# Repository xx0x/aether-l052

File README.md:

# Æther L052

A development board using the STM32L052K8Ux, optimized for low-power use. Its form factor matches the Adafruit Feather series.

## Schematic

*Click to see the full-size PDF*

## Specifications

### Microcontroller

| Name             | STM32L052K8Ux       |
| ---------------- | ------------------- |
| Core             | ARM Cortex M0+      |
| Flash Size       | 64 kB               |
| RAM Size         | 8 kB                |
| Clock Frequency  | 32 MHz              |
| Peripherals      | USB, SPI, I2C, UART |
| External Crystal | None                |

STM32L052K8U6 = –40 to 85 °C  
STM32L052K8U7 = –40 to 105 °C  
STM32L052K8U3 = –40 to 125 °C  

### Voltage Regulator

| Name              | MCP1711T-33I/OT |
| ----------------- | --------------- |
| Output Voltage    | 3.3 V           |
| Output Current    | 150 mA          |
| Quiescent Current | 600 nA          |

### Lithium Battery Charger

| Name           | MCP73832T-2ACI/OT     |
| -------------- | --------------------- |
| Charge Current | 100 mA (set using R4) |
| Charge State   | Available through PB8 |

## Why it exists?

There was no entry-level development board for the STM32L052 series, especially for the compact STM32L052K8Ux variant.

## Where to get it?

Æther L052 is open source and not sold in shops. You can build your own; all required files are in the `pcb` folder. If you are a manufacturer, you may reuse the design under the License, or contact me first if you prefer.

## Code examples

Look at the [Æther L052 Examples](https://github.com/xx0x/aether-l052-examples) repository.

## License

CERN-OHL-P-2.0 license

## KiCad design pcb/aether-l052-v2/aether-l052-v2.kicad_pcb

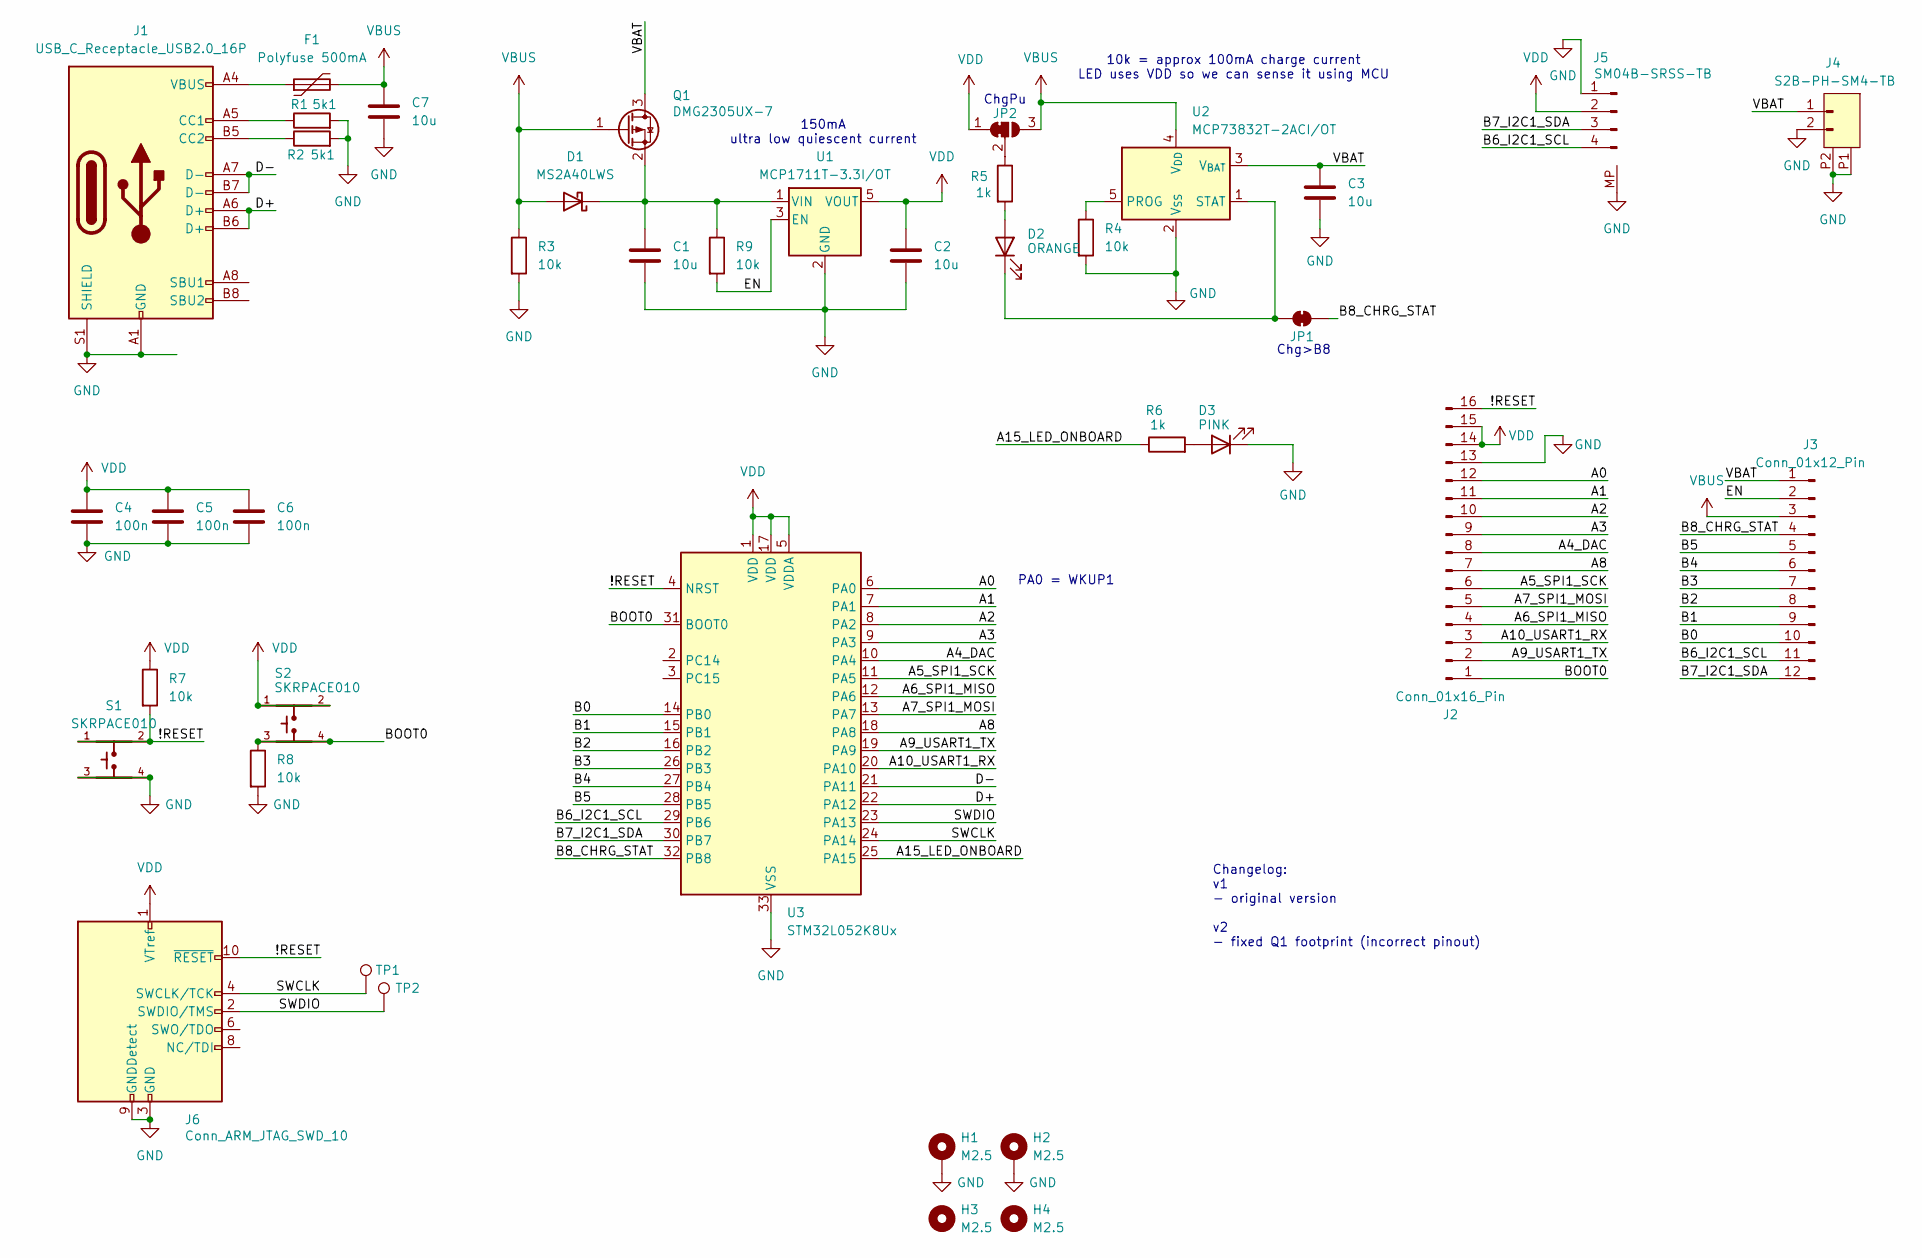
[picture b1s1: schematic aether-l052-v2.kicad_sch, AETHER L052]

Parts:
C1, C2, C3, C7: 10u; C_0805_2012Metric; LCSC C15850
C4, C5, C6: 100n; C_0603_1608Metric; LCSC C14663
D1: MS2A40LWS; D_SOD-323; LCSC C7380001
D2: ORANGE; LED_0603_1608Metric; LCSC C2286
D3: PINK; LED_0603_1608Metric; LCSC C2290
F1: Polyfuse 500mA; Fuse_0805_2012Metric; LCSC C883109
H1, H2: M2.5; MountingHole_2.5mm_Pad_Small
H3, H4: M2.5; MountingHole_2.5mm
J1: USB_C_Receptacle_USB2.0_16P; USB_C_Receptacle_XKB_U262-16XN-4BVC11; LCSC C393939
J2: Conn_01x16_Pin; PinHeader_1x16_P2.54mm_Vertical_NoSilk
J3: Conn_01x12_Pin; PinHeader_1x12_P2.54mm_Vertical_NoSilk
J4: S2B-PH-SM4-TB; S2B-PH-SM4-TB_LF__SN_; LCSC C295747
J5: SM04B-SRSS-TB; JST_SH_SM04B-SRSS-TB_1x04-1MP_P1.00mm_Horizontal; LCSC C160404
J6: Conn_ARM_JTAG_SWD_10; PinHeader_2x05_P1.27mm_Vertical_SMD; LCSC C41376037
JP1: SolderJumper_2_Bridged; SolderJumper-2_P1.3mm_Bridged_RoundedPad1.0x1.5mm
JP2: SolderJumper_3_Bridged12; SolderJumper-3_P1.3mm_Bridged12_RoundedPad1.0x1.5mm
Q1: DMG2305UX-7; SOT-23
R1, R2: 5k1; R_0603_1608Metric; LCSC C23186
R3, R4, R7, R8, R9: 10k; R_0603_1608Metric; LCSC C25804
R5, R6: 1k; R_0603_1608Metric; LCSC C21190
S1, S2: SKRPACE010; LCSC C139797
TP1: SWCLK; TestPoint_Pad_D2.0mm
TP2: SWDIO; TestPoint_Pad_D2.0mm
U1: MCP1711T-3.3I/OT; SOT-23-5; LCSC C79527
U2: MCP73832T-2ACI/OT; SOT-23-5; LCSC C38066
U3: STM32L052K8Ux; QFN-32-1EP_5x5mm_P0.5mm_EP3.45x3.45mm; LCSC C1342049

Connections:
/!RESET: J2.16, J6.10 (~RESET), R7.2, S1.1, S1.2, U3.4 (NRST)
/A0: J2.12, U3.6 (PA0)
/A1: J2.11, U3.7 (PA1)
/A2: J2.10, U3.8 (PA2)
/A3: J2.9, U3.9 (PA3)
/A4_DAC: J2.8, U3.10 (PA4)
/A5_SPI1_SCK: J2.6, U3.11 (PA5)
/A6_SPI1_MISO: J2.4, U3.12 (PA6)
/A7_SPI1_MOSI: J2.5, U3.13 (PA7)
/A8: J2.7, U3.18 (PA8)
/A9_USART1_TX: J2.2, U3.19 (PA9)
/A10_USART1_RX: J2.3, U3.20 (PA10)
/A15_LED_ONBOARD: R6.1, U3.25 (PA15)
/B0: J3.10, U3.14 (PB0)
/B1: J3.9, U3.15 (PB1)
/B2: J3.8, U3.16 (PB2)
/B3: J3.7, U3.26 (PB3)
/B4: J3.6, U3.27 (PB4)
/B5: J3.5, U3.28 (PB5)
/B6_I2C1_SCL: J3.11, J5.4, U3.29 (PB6)
/B7_I2C1_SDA: J3.12, J5.3, U3.30 (PB7)
/B8_CHRG_STAT: J3.4, JP1.2 (B), U3.32 (PB8)
/BOOT0: J2.1, R8.1, S2.3, S2.4, U3.31 (BOOT0)
/D+: J1.A6 (D+), J1.B6 (D+), U3.22 (PA12)
/D-: J1.A7 (D-), J1.B7 (D-), U3.21 (PA11)
/EN: J3.2, R9.2, U1.3 (EN)
/SWCLK: J6.4 (SWCLK/TCK), TP1.1, U3.24 (PA14)
/SWDIO: J6.2 (SWDIO/TMS), TP2.1, U3.23 (PA13)
/VBAT: C3.1, J3.1, J4.1, Q1.3 (D), U2.3 (V_{BAT})
GND: C1.2, C2.2, C3.2, C4.2, C5.2, C6.2, C7.2, D3.1 (K), H1.1, H2.1, J1.A1 (GND), J1.A12 (GND), J1.B1 (GND), J1.B12 (GND), J1.S1 (SHIELD), J2.13, J4.2, J4.P1, J4.P2, J5.1, J5.MP, J6.3 (GND), J6.5 (GND), J6.9 (GNDDetect), R1.2, R2.2, R3.2, R4.2, R8.2, S1.3, S1.4, U1.2 (GND), U2.2 (V_{SS}), U3.33 (VSS)
unnamed: C1.1, D1.1 (K), Q1.2 (S), R9.1, U1.1 (VIN)
unnamed: D2.2 (A), R5.2
unnamed: D2.1 (K), JP1.1 (A), U2.1 (STAT)
unnamed: D3.2 (A), R6.2
unnamed: F1.1, J1.A4 (VBUS), J1.A9 (VBUS), J1.B4 (VBUS), J1.B9 (VBUS)
unnamed: J1.A5 (CC1), R1.1
unnamed: J1.B5 (CC2), R2.1
unnamed: JP2.2 (C), R5.1
unnamed: R4.1, U2.5 (PROG)
VBUS: C7.1, D1.2 (A), F1.2, J3.3, JP2.3 (B), Q1.1 (G), R3.1, U2.4 (V_{DD})
VDD: C2.1, C4.1, C5.1, C6.1, J2.14, J2.15, J5.2, J6.1 (VTref), JP2.1 (A), R7.1, S2.1, S2.2, U1.5 (VOUT), U3.1 (VDD), U3.5 (VDDA), U3.17 (VDD)

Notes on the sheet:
150mA ultra low quiescent current
ChgPu
Changelog: v1 - original version v2 - fixed Q1 footprint (incorrect pinout)
10k = approx 100mA charge current LED uses VDD so we can sense it using MCU
PA0 = WKUP1
Chg>B8

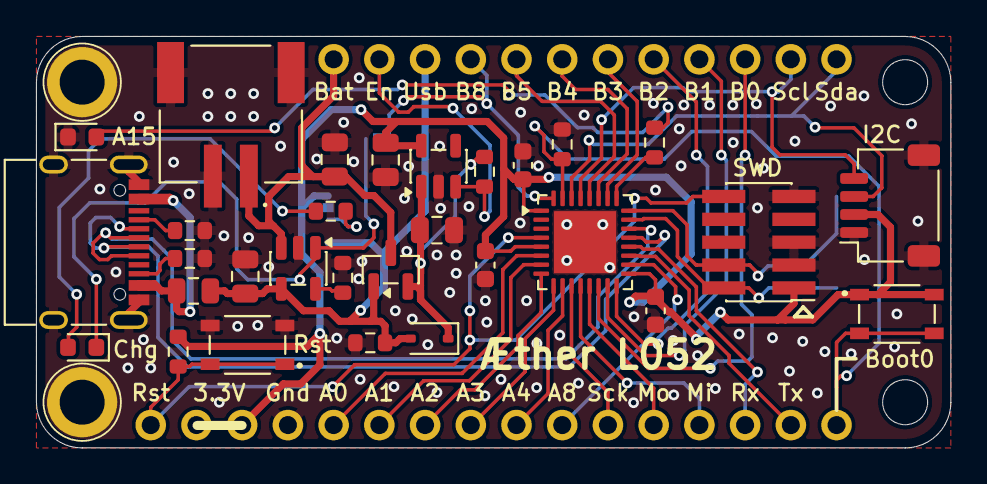
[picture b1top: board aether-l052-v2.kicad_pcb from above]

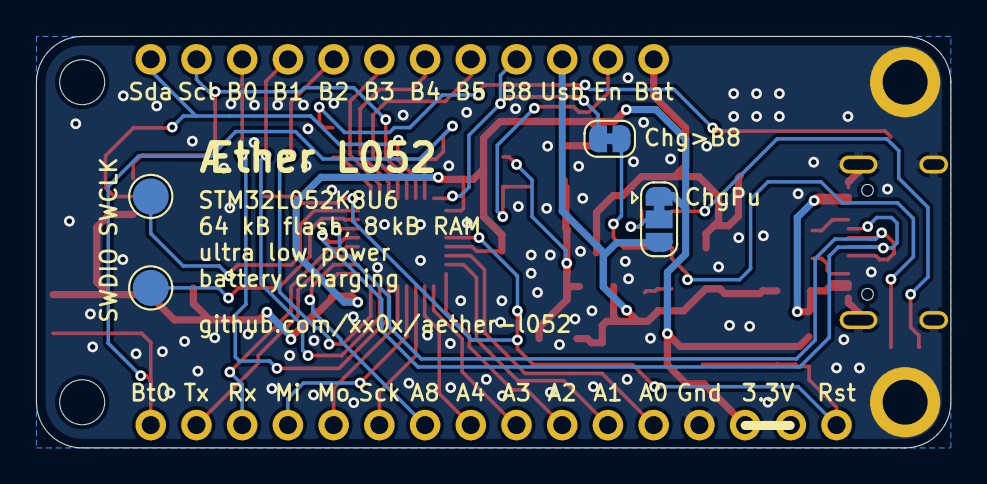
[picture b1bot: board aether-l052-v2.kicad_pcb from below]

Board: 2 copper layers, 50.8 x 22.9 mm, 40 parts (6 on the bottom side), 41 nets.

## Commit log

2025-10-04 initial sketches
2025-10-05 schematic, board layout in progress
2025-10-05 add license
2025-10-08 routing
2025-10-10 routing tweaks
2025-10-10 finishing board, add gerber, bom, cpl
2025-10-23 add readme and photo
2025-10-23 reorder the readme
2025-10-23 update readme texts
2025-10-24 add temperature ranges, change link
2025-10-25 add v2, fixes
